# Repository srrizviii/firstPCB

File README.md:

# First PCB – Eco-Car Onboarding PCB

A basic PCB designed in **KiCad 10.0** as my onboarding project for **UAlberta Eco-Car**. The goal was to learn the complete PCB workflow (schematic capture, footprint selection, layout, design rules, and fabrication outputs) before contributing to the team's electrical systems.

## Overview

Built without a specific purpose in mind, more of a general development board, with a USB-C connector, 4 push buttons, 10 configurable LEDs, connections for I2C, SPI, a mini OLED screen, and general purpose pins so external modules can communicate with the MCU (STM32F103C8Tx).

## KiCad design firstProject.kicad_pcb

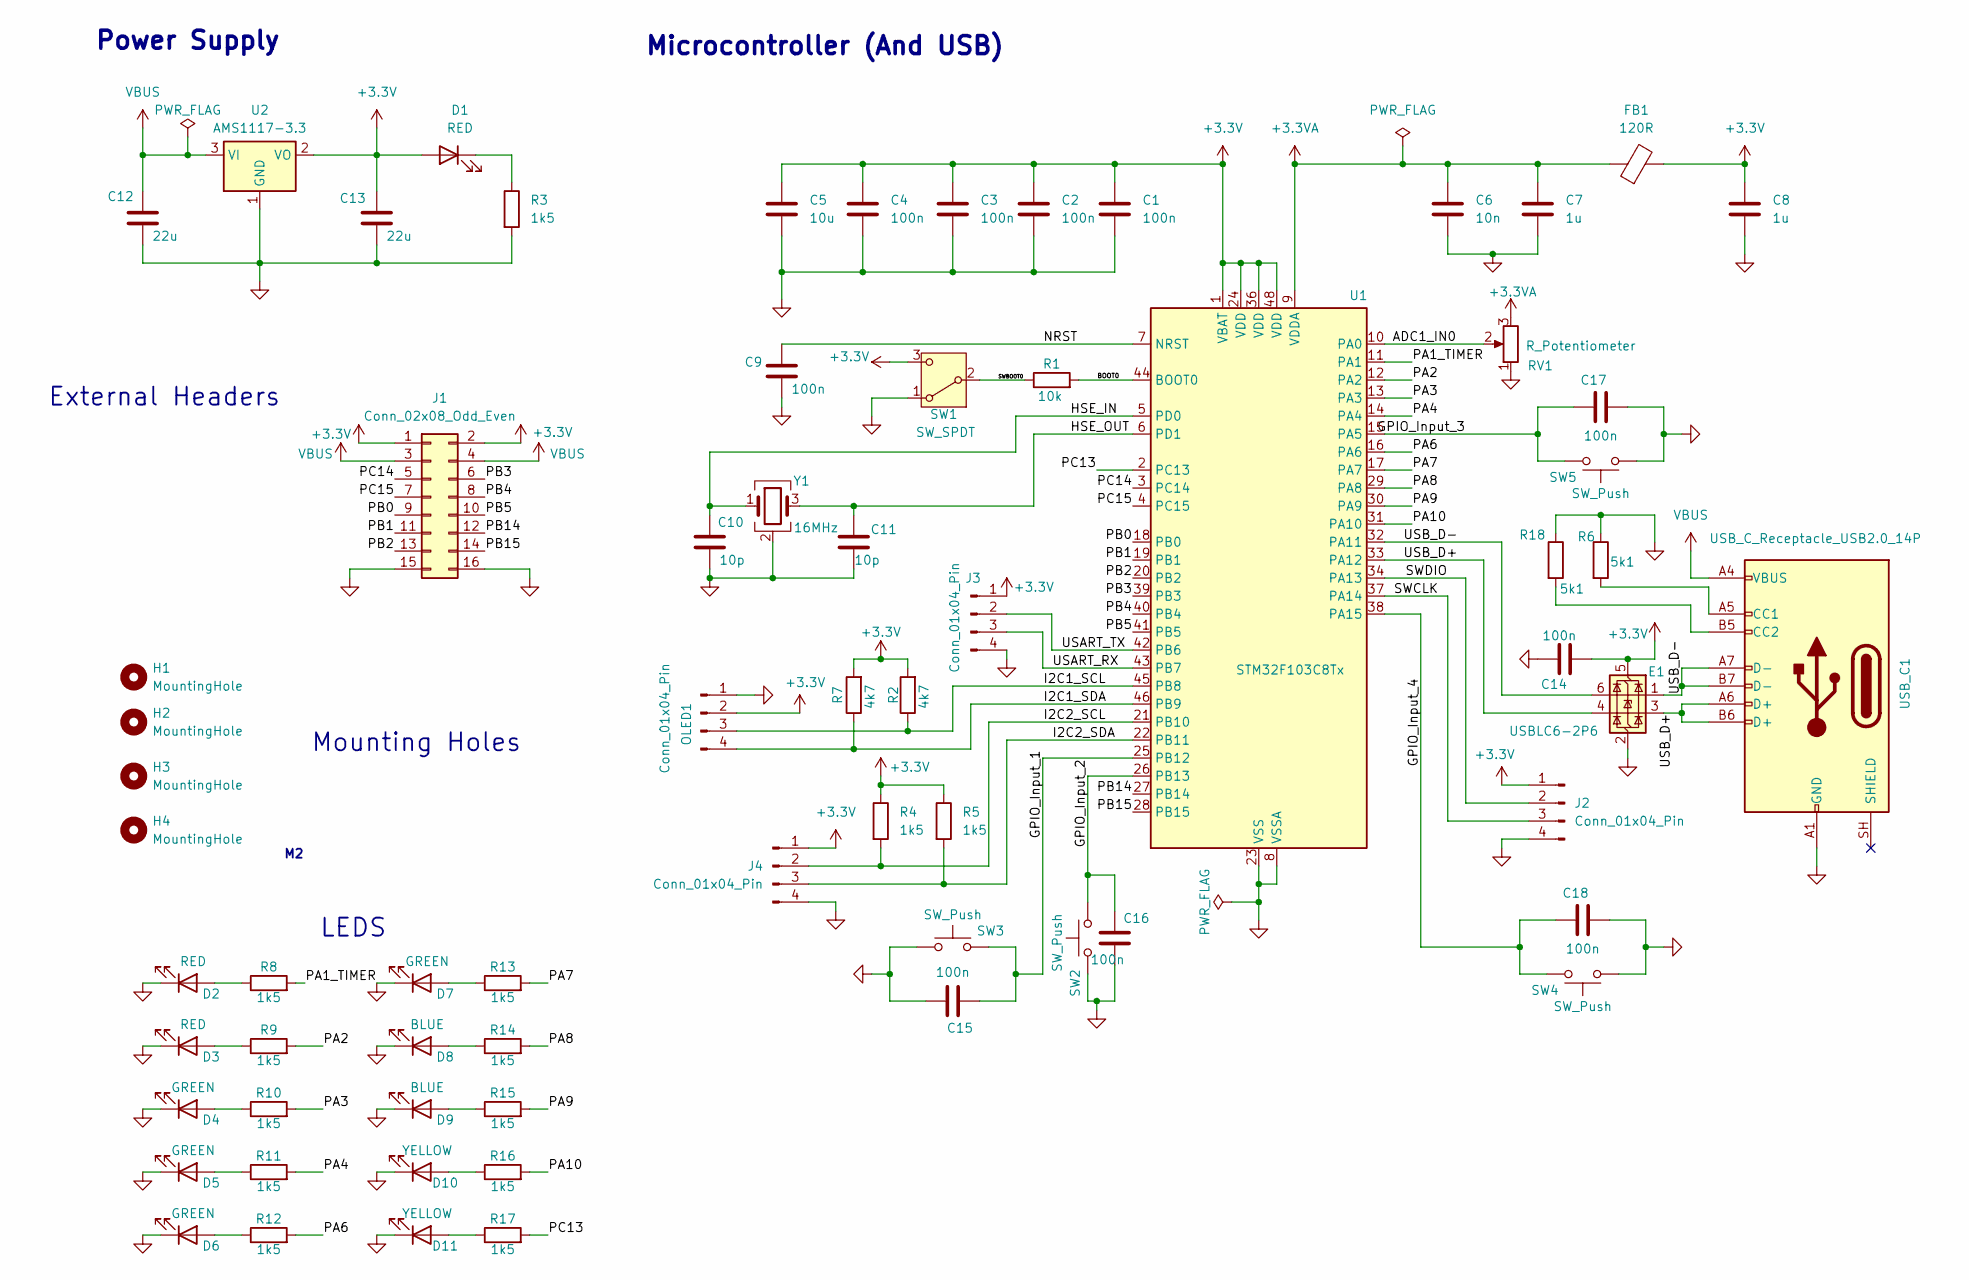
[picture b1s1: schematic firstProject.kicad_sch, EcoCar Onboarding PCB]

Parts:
C1, C2, C3, C4, C9, C14, C15, C16, C17, C18: 100n; C_0603_1608Metric
C5: 10u; C_0603_1608Metric
C6: 10n; C_0603_1608Metric
C7, C8: 1u; C_0603_1608Metric
C10, C11: 10p; C_0603_1608Metric
C12, C13: 22u; C_0603_1608Metric
D1, D2, D3: RED; LED_0603_1608Metric
D4, D5, D6, D7: GREEN; LED_0603_1608Metric
D8, D9: BLUE; LED_0603_1608Metric
D10, D11: YELLOW; LED_0603_1608Metric
E1: USBLC6-2P6; SOT-666
FB1: 120R; L_0603_1608Metric
H1, H2, H3, H4: MountingHole; MountingHole_2.2mm_M2
J1: Conn_02x08_Odd_Even; PinHeader_2x08_P2.54mm_Vertical
J2, J3, J4: Conn_01x04_Pin; PinHeader_1x04_P2.54mm_Vertical
OLED1: Conn_01x04_Pin; PinHeader_1x04_P2.54mm_Vertical
R1: 10k; R_0603_1608Metric
R2, R7: 4k7; R_0603_1608Metric
R3, R4, R5, R8, R9, R10, R11, R12, R13, R14, R15, R16, R17: 1k5; R_0603_1608Metric
R6, R18: 5k1; R_0603_1608Metric
RV1: R_Potentiometer; MSOP-8_3x3mm_P0.65mm
SW1: SW_SPDT; SW_SPDT_PCM12
SW2, SW3, SW4, SW5: SW_Push; SW_PUSH_6mm
U1: STM32F103C8Tx; LQFP-48_7x7mm_P0.5mm
U2: AMS1117-3.3; SOT-223-3_TabPin2
USB_C1: USB_C_Receptacle_USB2.0_14P; USB_C_Receptacle_HRO_TYPE-C-31-M-12
Y1: 16MHz; Crystal_SMD_3225-4Pin_3.2x2.5mm

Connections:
+3.3V: C1.1, C2.1, C3.1, C4.1, C5.1, C8.1, C13.1, C14.2, D1.2 (A), E1.5 (VBUS), FB1.2, J1.1, J1.2, J2.1, J3.1, J4.1, OLED1.2, R2.2, R4.1, R5.1, R7.2, SW1.3 (C), U1.1 (VBAT), U1.24 (VDD), U1.36 (VDD), U1.48 (VDD), U2.2 (VO)
+3.3VA: C6.1, C7.1, FB1.1, RV1.3, U1.9 (VDDA)
/ADC1_IN0: RV1.2, U1.10 (PA0)
/BOOT0: R1.2, U1.44 (BOOT0)
/GPIO_Input_1: C15.2, SW3.2, U1.25 (PB12)
/GPIO_Input_2: C16.2, SW2.2, U1.26 (PB13)
/GPIO_Input_3: C17.2, SW5.2, U1.15 (PA5)
/GPIO_Input_4: C18.2, SW4.2, U1.38 (PA15)
/HSE_IN: C10.1, U1.5 (PD0), Y1.1
/HSE_OUT: C11.1, U1.6 (PD1), Y1.3
/I2C1_SCL: OLED1.3, R2.1, U1.45 (PB8)
/I2C1_SDA: OLED1.4, R7.1, U1.46 (PB9)
/I2C2_SCL: J4.2, R4.2, U1.21 (PB10)
/I2C2_SDA: J4.3, R5.2, U1.22 (PB11)
/NRST: C9.1, U1.7 (NRST)
/PA1_TIMER: R8.2, U1.11 (PA1)
/PA2: R9.2, U1.12 (PA2)
/PA3: R10.2, U1.13 (PA3)
/PA4: R11.2, U1.14 (PA4)
/PA6: R12.2, U1.16 (PA6)
/PA7: R13.2, U1.17 (PA7)
/PA8: R14.2, U1.29 (PA8)
/PA9: R15.2, U1.30 (PA9)
/PA10: R16.2, U1.31 (PA10)
/PB0: J1.9, U1.18 (PB0)
/PB1: J1.11, U1.19 (PB1)
/PB2: J1.13, U1.20 (PB2)
/PB3: J1.6, U1.39 (PB3)
/PB4: J1.8, U1.40 (PB4)
/PB5: J1.10, U1.41 (PB5)
/PB14: J1.12, U1.27 (PB14)
/PB15: J1.14, U1.28 (PB15)
/PC13: R17.2, U1.2 (PC13)
/PC14: J1.5, U1.3 (PC14)
/PC15: J1.7, U1.4 (PC15)
/SWBOOT0: R1.1, SW1.2 (B)
/SWCLK: J2.3, U1.37 (PA14)
/SWDIO: J2.2, U1.34 (PA13)
/USART_RX: J3.3, U1.43 (PB7)
/USART_TX: J3.2, U1.42 (PB6)
/USB_D+: E1.3 (I/O2), E1.4 (I/O2), U1.33 (PA12), USB_C1.A6 (D+), USB_C1.B6 (D+)
/USB_D-: E1.1 (I/O1), E1.6 (I/O1), U1.32 (PA11), USB_C1.A7 (D-), USB_C1.B7 (D-)
GND: C1.2, C2.2, C3.2, C4.2, C5.2, C6.2, C7.2, C8.2, C9.2, C10.2, C11.2, C12.2, C13.2, C14.1, C15.1, C16.1, C17.1, C18.1, D2.1 (K), D3.1 (K), D4.1 (K), D5.1 (K), D6.1 (K), D7.1 (K), D8.1 (K), D9.1 (K), D10.1 (K), D11.1 (K), E1.2 (GND), J1.15, J1.16, J2.4, J3.4, J4.4, OLED1.1, R3.2, R6.1, R18.1, RV1.1, SW1.1 (A), SW2.1, SW3.1, SW4.1, SW5.1, U1.8 (VSSA), U1.23 (VSS), U1.35 (VSS), U1.47 (VSS), U2.1 (GND), USB_C1.A1 (GND), USB_C1.A12 (GND), USB_C1.B1 (GND), USB_C1.B12 (GND), Y1.2 (G), Y1.4 (G)
unnamed: D1.1 (K), R3.1
unnamed: D2.2 (A), R8.1
unnamed: D3.2 (A), R9.1
unnamed: D4.2 (A), R10.1
unnamed: D5.2 (A), R11.1
unnamed: D6.2 (A), R12.1
unnamed: D7.2 (A), R13.1
unnamed: D8.2 (A), R14.1
unnamed: D9.2 (A), R15.1
unnamed: D10.2 (A), R16.1
unnamed: D11.2 (A), R17.1
unnamed: R6.2, USB_C1.A5 (CC1)
unnamed: R18.2, USB_C1.B5 (CC2)
VBUS: C12.1, J1.3, J1.4, U2.3 (VI), USB_C1.A4 (VBUS), USB_C1.A9 (VBUS), USB_C1.B4 (VBUS), USB_C1.B9 (VBUS)

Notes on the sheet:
External Headers
LEDS
Mounting Holes
Microcontroller (And USB)
Power Supply

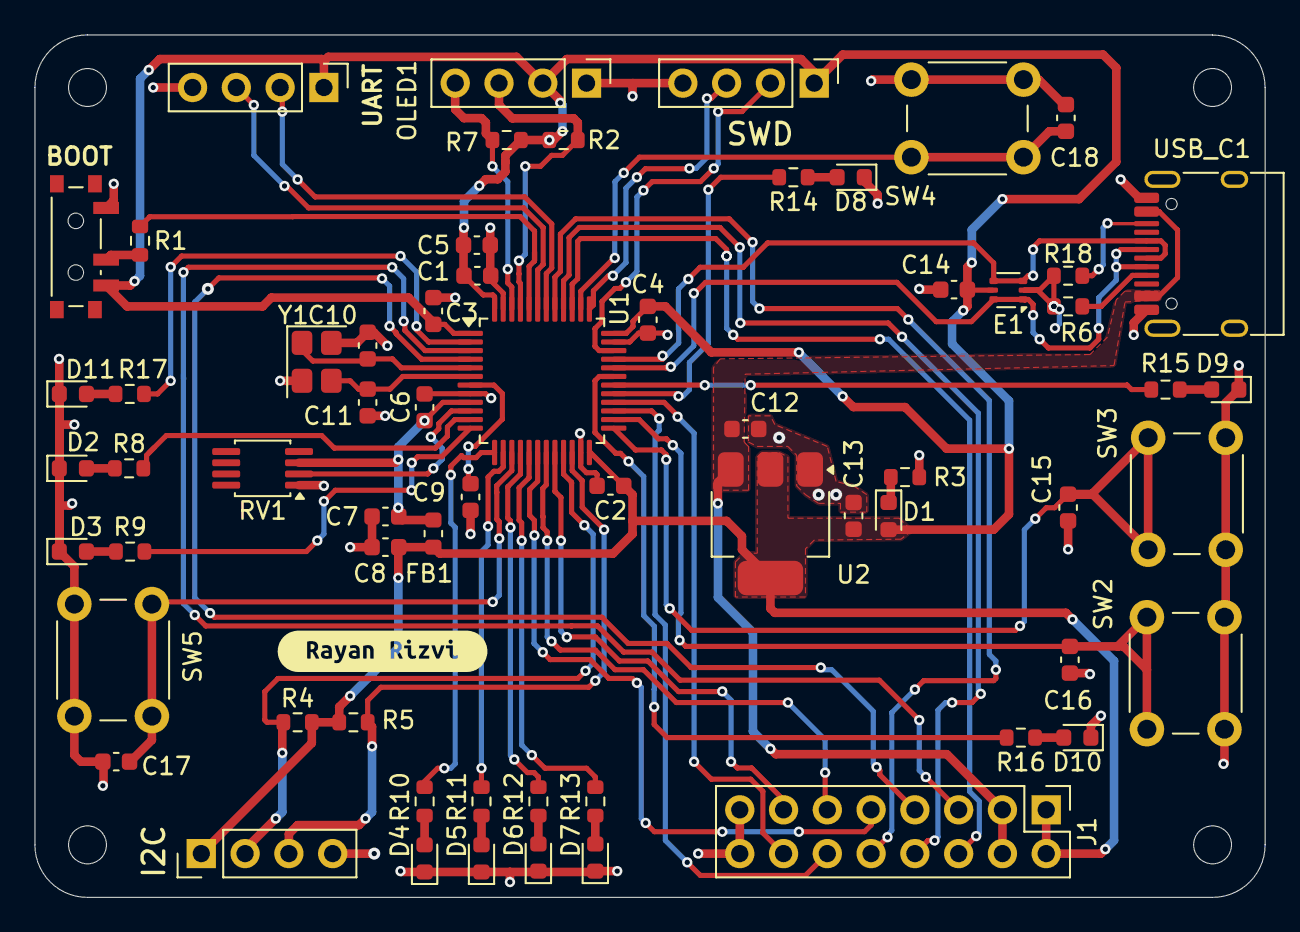
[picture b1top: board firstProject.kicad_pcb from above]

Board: 2 copper layers, 71.4 x 50.0 mm, 69 parts (0 on the bottom side), 57 nets.

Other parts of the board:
kibuzzard-6ADD32FB: G***; kibuzzard-6ADD32FB

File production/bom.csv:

Designator,Footprint,Quantity,Value,LCSC Part #
"C1, C14, C15, C16, C17, C18, C2, C3, C4, C9",0603,10,100n,
"C10, C11",0603,2,10p,
"C12, C13",0603,2,22u,
C5,0603,1,10u,
C6,0603,1,10n,
"C7, C8",0603,2,1u,
"D1, D2, D3",0603,3,RED,
"D10, D11",0603,2,YELLOW,
"D4, D5, D6, D7",0603,4,GREEN,
"D8, D9",0603,2,BLUE,
E1,SOT-666,1,USBLC6-2P6,
FB1,0603,1,120R,
J1,PinHeader_2x08_P2.54mm_Vertical,1,Conn_02x08_Odd_Even,
"J2, J3, J4, OLED1",PinHeader_1x04_P2.54mm_Vertical,4,Conn_01x04_Pin,
R1,0603,1,10k,
"R10, R11, R12, R13, R14, R15, R16, R17, R3, R4, R5, R8, R9",0603,13,1k5,
"R18, R6",0603,2,5k1,
"R2, R7",0603,2,4k7,
RV1,MSOP-8_3x3mm_P0.65mm,1,R_Potentiometer,
SW1,SW_SPDT_PCM12,1,SW_SPDT,
"SW2, SW3, SW4, SW5",SW_PUSH_6mm,4,SW_Push,
U1,LQFP-48_7x7mm_P0.5mm,1,STM32F103C8Tx,
U2,SOT-223-3_TabPin2,1,AMS1117-3.3,
USB_C1,USB_C_Receptacle_HRO_TYPE-C-31-M-12,1,USB_C_Receptacle_USB2.0_14P,
Y1,Crystal_SMD_3225-4Pin_3.2x2.5mm,1,16MHz,
